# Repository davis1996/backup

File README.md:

# backup

this is a change for homework

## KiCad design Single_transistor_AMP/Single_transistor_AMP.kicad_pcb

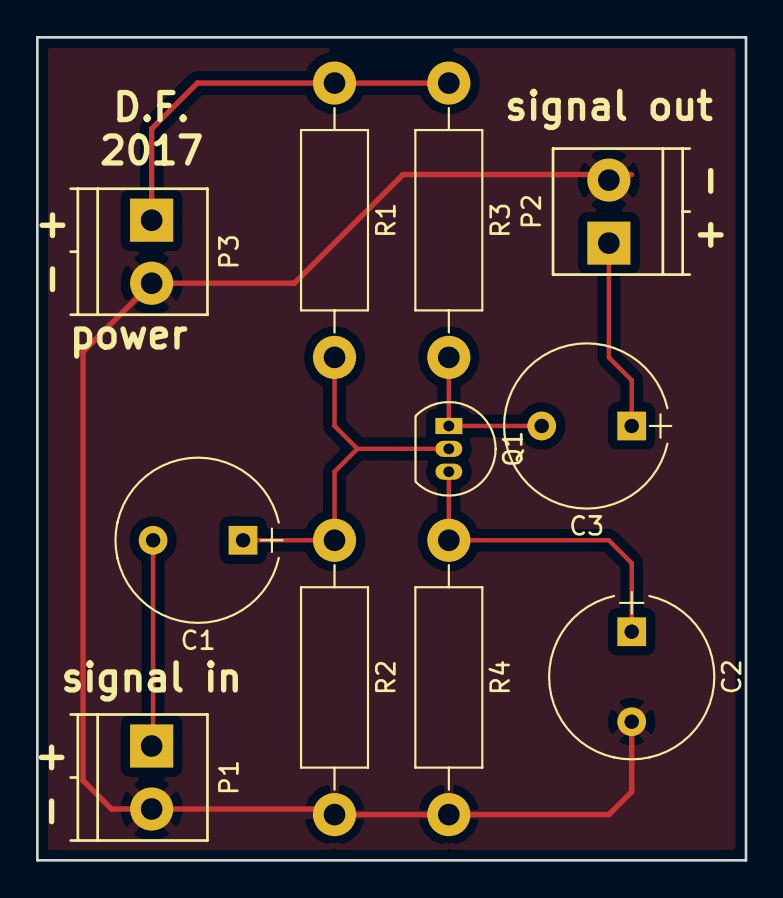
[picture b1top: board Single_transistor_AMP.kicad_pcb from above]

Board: 2 copper layers, 39.4 x 45.7 mm, 11 parts (0 on the bottom side), 7 nets.

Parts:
C1, C3: 20uF; CP_Radial_Tantal_D9.0mm_P5.00mm
C2: 50uF; CP_Radial_Tantal_D9.0mm_P5.00mm
P1: Input; TerminalBlock_Pheonix_PT-3.5mm_2pol
P2: output; TerminalBlock_Pheonix_PT-3.5mm_2pol
P3: power; TerminalBlock_Pheonix_PT-3.5mm_2pol
Q1: BC548; TO-92_Inline_Narrow_Oval
R1: 22k; R_Axial_DIN0411_L9.9mm_D3.6mm_P15.24mm_Horizontal
R2: 6.8k; R_Axial_DIN0411_L9.9mm_D3.6mm_P15.24mm_Horizontal
R3: 4.7k; R_Axial_DIN0411_L9.9mm_D3.6mm_P15.24mm_Horizontal
R4: 1.8k; R_Axial_DIN0411_L9.9mm_D3.6mm_P15.24mm_Horizontal

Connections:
+12V: P3.1, R1.1, R3.1
GND: C2.2, P1.2, P2.2, P3.2, R2.2, R4.2
unnamed: C1.1, Q1.2, R1.2, R2.1
unnamed: C1.2, P1.1
unnamed: C2.1, Q1.3, R4.1
unnamed: C3.1, P2.1
unnamed: C3.2, Q1.1, R3.2

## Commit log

2017-03-02 izmainas veiktas readme
2017-03-07 Readme update, just for test and homework
2017-03-15 md pabeigts
2017-03-22 md nav pabeigts pagaidaam
2017-03-26 md2 pabeigts
2017-03-27 md3 pabeigts
2017-03-29 PWR_supply labojumi veikti
2017-03-30 izveidots klases tarbs Battery
2017-05-10 pabeigts maajas darbs battery un iesaakts projekts controll unit
2017-05-11 Single transistor amp pabeigs komponensu layout
2017-05-18 Single transistor amp pabeigta plate
2017-05-18 Single transistor amp pabeigti gerbera faili
2017-06-17 Pabeigts kursa darbs Controll_unit
